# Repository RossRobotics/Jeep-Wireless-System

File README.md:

# Jeep Wireless System
##Adding Wireless features for exterior lights on a Jeep Wrangler TJ.  All related files will be in this Repository.

#Wireless Features Include:
* Parking lights
* LED Fog Lights
* LED Light Bar
* Rock Lights: These will be WS2812 RGB LED Custom Strips
* LED Reverse Lights

##As of March 1st, PCB version is 0.2 and is posted here.

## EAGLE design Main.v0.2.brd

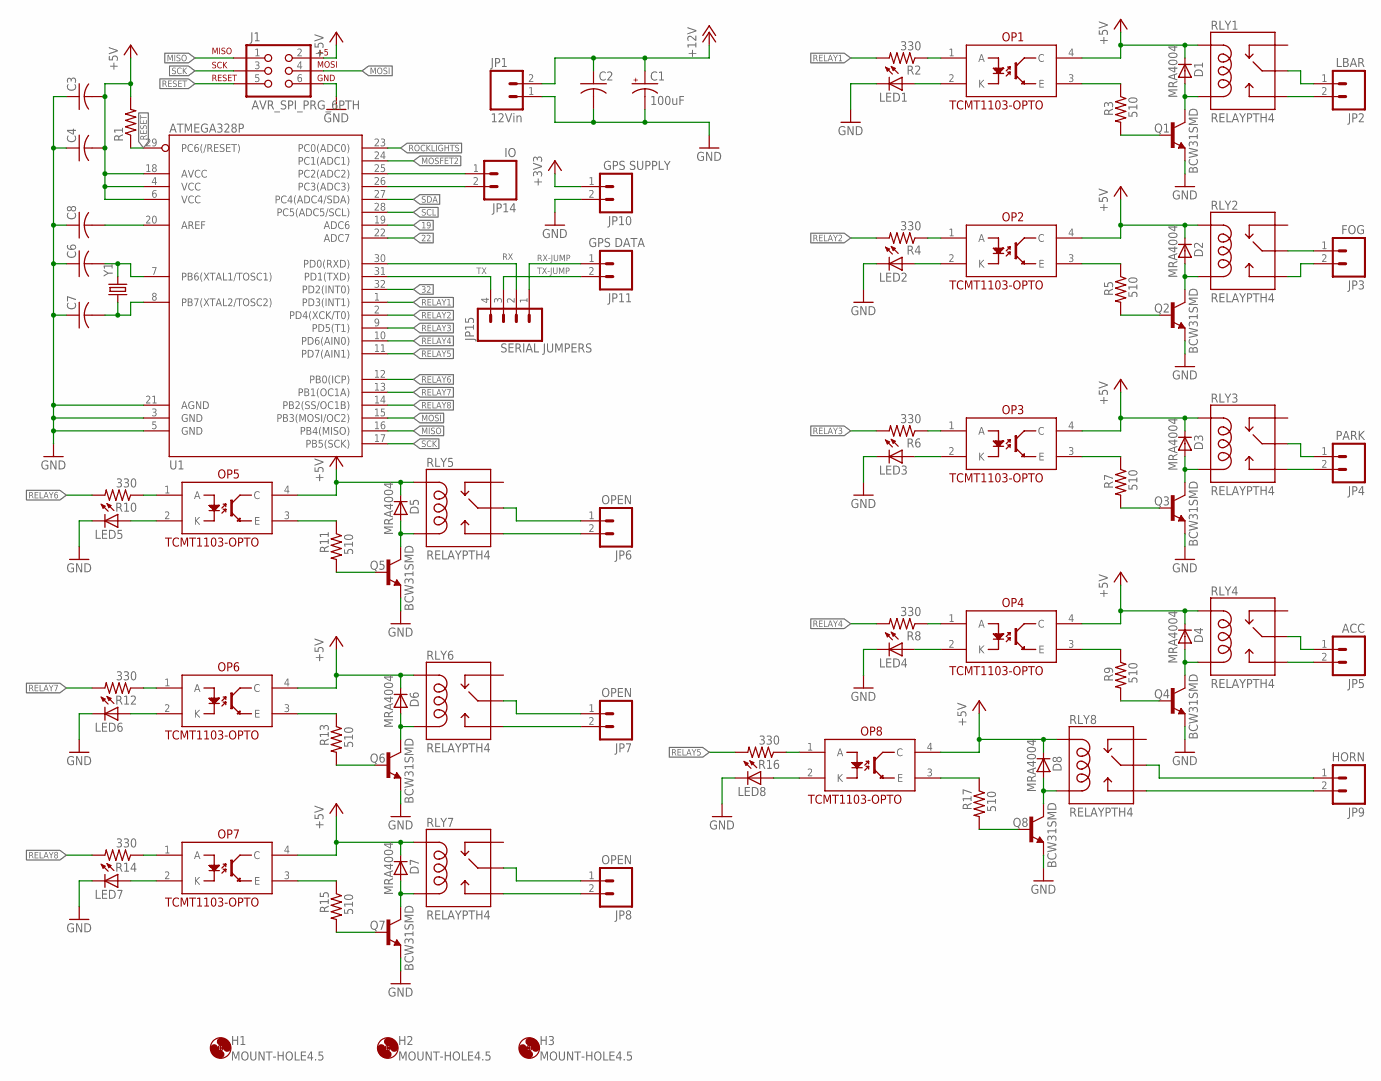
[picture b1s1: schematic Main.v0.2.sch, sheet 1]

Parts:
C1: 100uF; PANASONIC_F
C2, C3, C4, C6, C7, C8: C-USC1206; C1206
D1, D2, D3, D4, D5, D6, D7, D8: MRA4004; SMA-DIODE_ALT
H1, H2, H3: MOUNT-HOLE4.5; 4,5
J1: AVR_SPI_PRG_6PTH; 2X3
JP1: 12Vin; SCREWTERMINAL-3.5MM-2
JP2: LBAR; SCREWTERMINAL-3.5MM-2
JP3: FOG; SCREWTERMINAL-3.5MM-2
JP4: PARK; SCREWTERMINAL-3.5MM-2
JP5: ACC; SCREWTERMINAL-3.5MM-2
JP6, JP7, JP8: OPEN; SCREWTERMINAL-3.5MM-2
JP9: HORN; SCREWTERMINAL-3.5MM-2
JP10: GPS SUPPLY; SCREWTERMINAL-3.5MM-2
JP11: GPS DATA; SCREWTERMINAL-3.5MM-2
JP14: IO; SCREWTERMINAL-3.5MM-2
JP15: SERIAL JUMPERS; 1X04
LED1, LED2, LED3, LED4, LED5, LED6, LED7, LED8: LED1206; LED-1206
OP1, OP2, OP3, OP4, OP5, OP6, OP7, OP8: TCMT1103-OPTO; SSOP-4
Q1, Q2, Q3, Q4, Q5, Q6, Q7, Q8: BCW31SMD; SOT23-BEC
R1: R-US_R1206; R1206
R2, R4, R6, R8, R10, R12, R14, R16: 330; R1206
R3, R5, R7, R9, R11, R13, R15, R17: 510; R1206
RLY1, RLY2, RLY3, RLY4, RLY5, RLY6, RLY7, RLY8: RELAYPTH4; RELAY-JZC
U1: ATMEGA328P; TQFP32-08
Y1: CRYSTALSMD; HC49UP

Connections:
19: U1.19 (ADC6); also elsewhere on the board
22: U1.22 (ADC7); also elsewhere on the board
32: U1.32 (PD2(INT0)); also elsewhere on the board
+3V3: JP10.1; also elsewhere on the board
+5V: C3.2, C4.2, D1.C, D2.C, D3.C, D4.C, D5.C, D6.C, D7.C, D8.C, J1.2, OP1.4 (C), OP2.4 (C), OP3.4 (C), OP4.4 (C), OP5.4 (C), OP6.4 (C), OP7.4 (C), OP8.4 (C), R1.2, RLY1.5 (COIL1), RLY2.5 (COIL1), RLY3.5 (COIL1), RLY4.5 (COIL1), RLY5.5 (COIL1), RLY6.5 (COIL1), RLY7.5 (COIL1), RLY8.5 (COIL1), U1.4 (VCC), U1.6 (VCC), U1.18 (AVCC); also elsewhere on the board
+12V: C1.+, C2.1, JP1.2; also elsewhere on the board
GND: C1.-, C2.2, C3.1, C4.1, C6.1, C7.1, C8.1, J1.6, JP1.1, JP10.2, LED1.C, LED2.C, LED3.C, LED4.C, LED5.C, LED6.C, LED7.C, LED8.C, Q1.E, Q2.E, Q3.E, Q4.E, Q5.E, Q6.E, Q7.E, Q8.E, U1.3 (GND), U1.5 (GND), U1.21 (AGND); also elsewhere on the board
MISO: J1.1, U1.16 (PB4(MISO))
MOSFET2: U1.24 (PC1(ADC1))
MOSI: J1.4, U1.15 (PB3(MOSI/OC2))
unnamed: LED6.A, OP6.2 (K)
unnamed: D1.A, Q1.C, RLY1.1 (COIL2)
unnamed: C6.2, U1.7 (PB6(XTAL1/TOSC1)), Y1.2
unnamed: C7.2, U1.8 (PB7(XTAL2/TOSC2)), Y1.1
unnamed: C8.2, U1.20 (AREF)
unnamed: Q1.B, R3.2
unnamed: OP1.3 (E), R3.1
unnamed: OP1.1 (A), R2.1
unnamed: LED1.A, OP1.2 (K)
unnamed: D2.A, Q2.C, RLY2.1 (COIL2)
unnamed: Q2.B, R5.2
unnamed: OP2.3 (E), R5.1
unnamed: OP2.1 (A), R4.1
unnamed: LED2.A, OP2.2 (K)
unnamed: D3.A, Q3.C, RLY3.1 (COIL2)
unnamed: Q3.B, R7.2
unnamed: OP3.3 (E), R7.1
unnamed: OP3.1 (A), R6.1
unnamed: LED3.A, OP3.2 (K)
unnamed: D4.A, Q4.C, RLY4.1 (COIL2)
unnamed: Q4.B, R9.2
unnamed: OP4.3 (E), R9.1
unnamed: OP4.1 (A), R8.1
unnamed: LED5.A, OP5.2 (K)
unnamed: D5.A, Q5.C, RLY5.1 (COIL2)
unnamed: Q5.B, R11.2
unnamed: OP5.3 (E), R11.1
unnamed: OP5.1 (A), R10.1
unnamed: LED4.A, OP4.2 (K)
unnamed: D6.A, Q6.C, RLY6.1 (COIL2)
unnamed: Q6.B, R13.2
unnamed: OP6.3 (E), R13.1
unnamed: OP6.1 (A), R12.1
unnamed: LED7.A, OP7.2 (K)
unnamed: D7.A, Q7.C, RLY7.1 (COIL2)
unnamed: Q7.B, R15.2
unnamed: OP7.3 (E), R15.1
unnamed: OP7.1 (A), R14.1
unnamed: LED8.A, OP8.2 (K)
unnamed: D8.A, Q8.C, RLY8.1 (COIL2)
unnamed: Q8.B, R17.2
unnamed: OP8.3 (E), R17.1
unnamed: OP8.1 (A), R16.1
unnamed: JP8.2, RLY7.3 (NO)
unnamed: JP9.2, RLY8.3 (NO)
unnamed: JP8.1, RLY7.4 (MAIN)
unnamed: JP7.1, RLY6.4 (MAIN)
unnamed: JP7.2, RLY6.3 (NO)
unnamed: JP6.2, RLY5.3 (NO)
unnamed: JP6.1, RLY5.4 (MAIN)
unnamed: JP9.1, RLY8.4 (MAIN)
unnamed: JP5.2, RLY4.3 (NO)
unnamed: JP5.1, RLY4.4 (MAIN)
unnamed: JP4.2, RLY3.3 (NO)
unnamed: JP4.1, RLY3.4 (MAIN)
unnamed: JP3.2, RLY2.3 (NO)
unnamed: JP3.1, RLY2.4 (MAIN)
unnamed: JP2.2, RLY1.3 (NO)
unnamed: JP2.1, RLY1.4 (MAIN)
unnamed: JP14.2, U1.26 (PC3(ADC3))
RELAY1: R2.2, U1.1 (PD3(INT1))
RELAY2: R4.2, U1.2 (PD4(XCK/T0))
RELAY3: R6.2, U1.9 (PD5(T1))
RELAY4: R8.2, U1.10 (PD6(AIN0))
RELAY5: R16.2, U1.11 (PD7(AIN1))
RELAY6: R10.2, U1.12 (PB0(ICP))
RELAY7: R12.2, U1.13 (PB1(OC1A))
RELAY8: R14.2, U1.14 (PB2(SS/OC1B))
RESET: J1.5, R1.1, U1.29 (PC6(/RESET))
RFID: JP14.1, U1.25 (PC2(ADC2))
ROCKLIGHTS: U1.23 (PC0(ADC0)); also elsewhere on the board
RX: JP15.2, U1.30 (PD0(RXD)); also elsewhere on the board
RX-JUMP: JP11.1, JP15.1
SCK: J1.3, U1.17 (PB5(SCK))
SCL: U1.28 (PC5(ADC5/SCL)); also elsewhere on the board
SDA: U1.27 (PC4(ADC4/SDA)); also elsewhere on the board
TX: JP15.4, U1.31 (PD1(TXD)); also elsewhere on the board
TX-JUMP: JP11.2, JP15.3

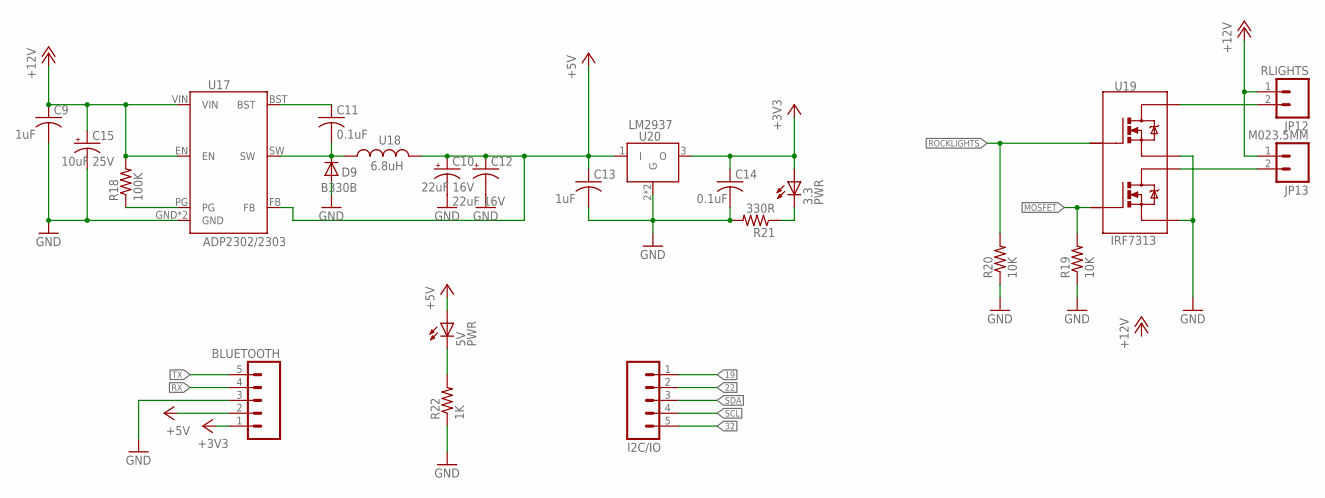
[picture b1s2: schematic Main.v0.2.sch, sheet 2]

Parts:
3.3, 5V: PWR; LED-1206
BLUETOOTH: M05PTH; 1X05
C9, C13: 1uF; C1206
C10, C12: 22uF 16V; PANASONIC_E
C11, C14: 0.1uF; C1206
C15: 10uF 25V; PANASONIC_E
D9: B330B; DO214AA
I2C/IO: M05PTH; 1X05
JP12: RLIGHTS; SCREWTERMINAL-3.5MM-2
JP13: M023.5MM; SCREWTERMINAL-3.5MM-2
R18: 100K; R1206
R19, R20: 10K; R1206
R21: 330R; R1206
R22: 1K; R1206
U17: ADP2302/2303; 8SOIC
U18: 6.8uH; INDUCTOR
U19: IRF7313; SO-8
U20: LM2937; SOT223

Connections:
19: I2C/IO.1; also elsewhere on the board
22: I2C/IO.2; also elsewhere on the board
32: I2C/IO.5; also elsewhere on the board
+3V3: 3.3.A, BLUETOOTH.1, C14.1, U20.3 (O); also elsewhere on the board
+5V: 5V.A, BLUETOOTH.2, C10.+, C12.+, C13.1, U17.FB, U18.P$2 (2), U20.1 (I); also elsewhere on the board
+12V: C9.1, C15.+, JP12.1, JP13.1, R18.2, U17.EN, U17.VIN; also elsewhere on the board
GND: BLUETOOTH.3, C9.2, C10.-, C12.-, C13.2, C14.2, C15.-, D9.A, R19.1, R20.1, R21.2, R22.1, U17.GND, U17.NC (GND), U19.1 (S), U19.3 (S1), U20.2 (G), U20.4 (G); also elsewhere on the board
MOSFET: R19.2, U19.4 (G1)
unnamed: JP12.2, U19.7 (D), U19.8 (D)
unnamed: JP13.2, U19.5 (D1), U19.6 (D1)
unnamed: R18.1, U17.PG
unnamed: 3.3.C, R21.1
unnamed: C11.1, U17.BST
unnamed: 5V.C, R22.2
ROCKLIGHTS: R20.2, U19.2 (G); also elsewhere on the board
RX: BLUETOOTH.4; also elsewhere on the board
SCL: I2C/IO.4; also elsewhere on the board
SDA: I2C/IO.3; also elsewhere on the board
SW: C11.2, D9.C, U17.SW, U18.P$1 (1)
TX: BLUETOOTH.5; also elsewhere on the board

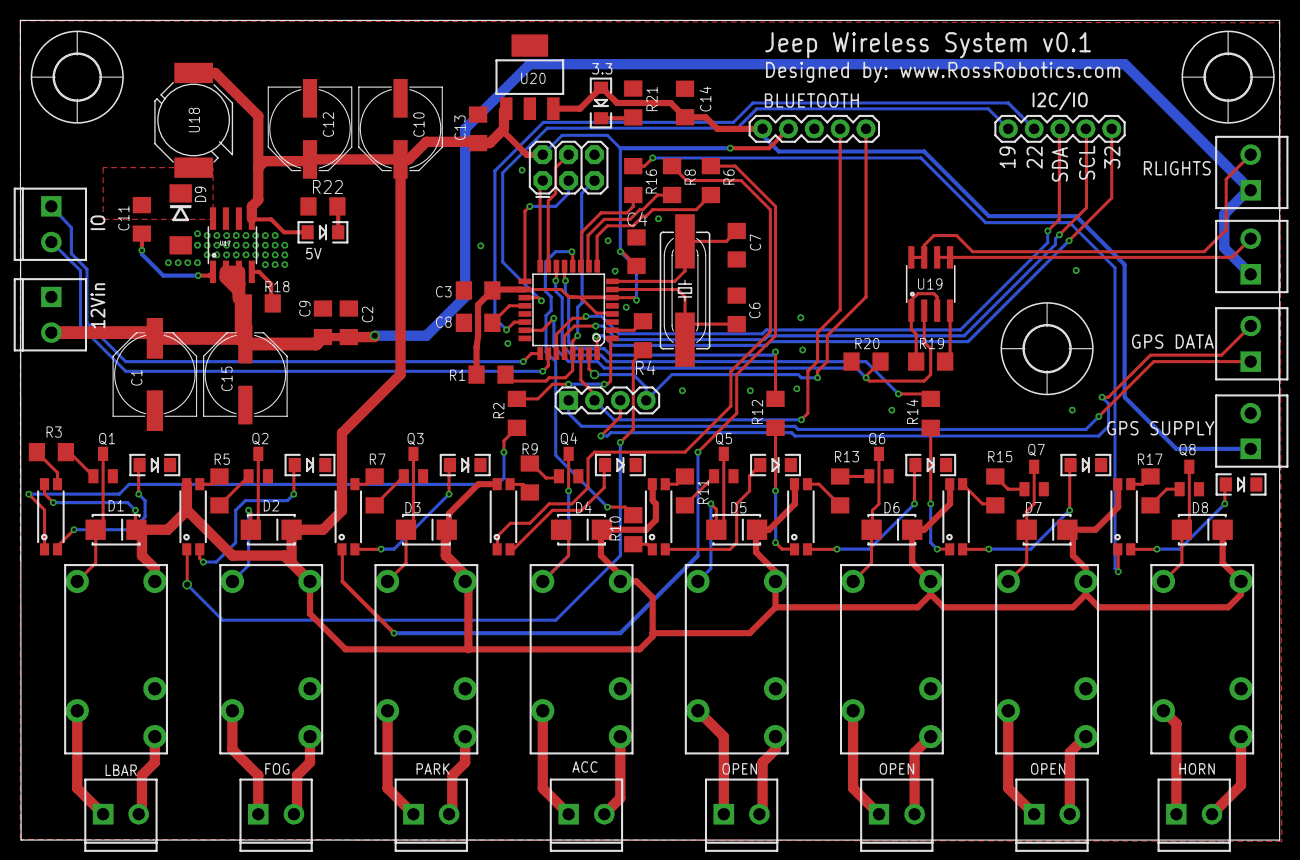
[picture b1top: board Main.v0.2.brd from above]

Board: 2 copper layers, 123.7 x 80.5 mm, 106 parts (0 on the bottom side), 95 nets.

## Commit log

2016-03-02 :boom::camel: Added .gitattributes & .gitignore files
2016-03-02 Schematic of main PCB board
    This is version 0.2 of the schematic.
2016-03-02 Board layout for the main board
    brd file from Eagle CAD v7.5
2016-03-02 Don't need it
2016-03-02 Created Readme
    Added detailed info

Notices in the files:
parts and their libraries:
SparkFun-LED: Licensing: CC v3.0 Share-Alike You are welcome to use this library for commercial purposes.
